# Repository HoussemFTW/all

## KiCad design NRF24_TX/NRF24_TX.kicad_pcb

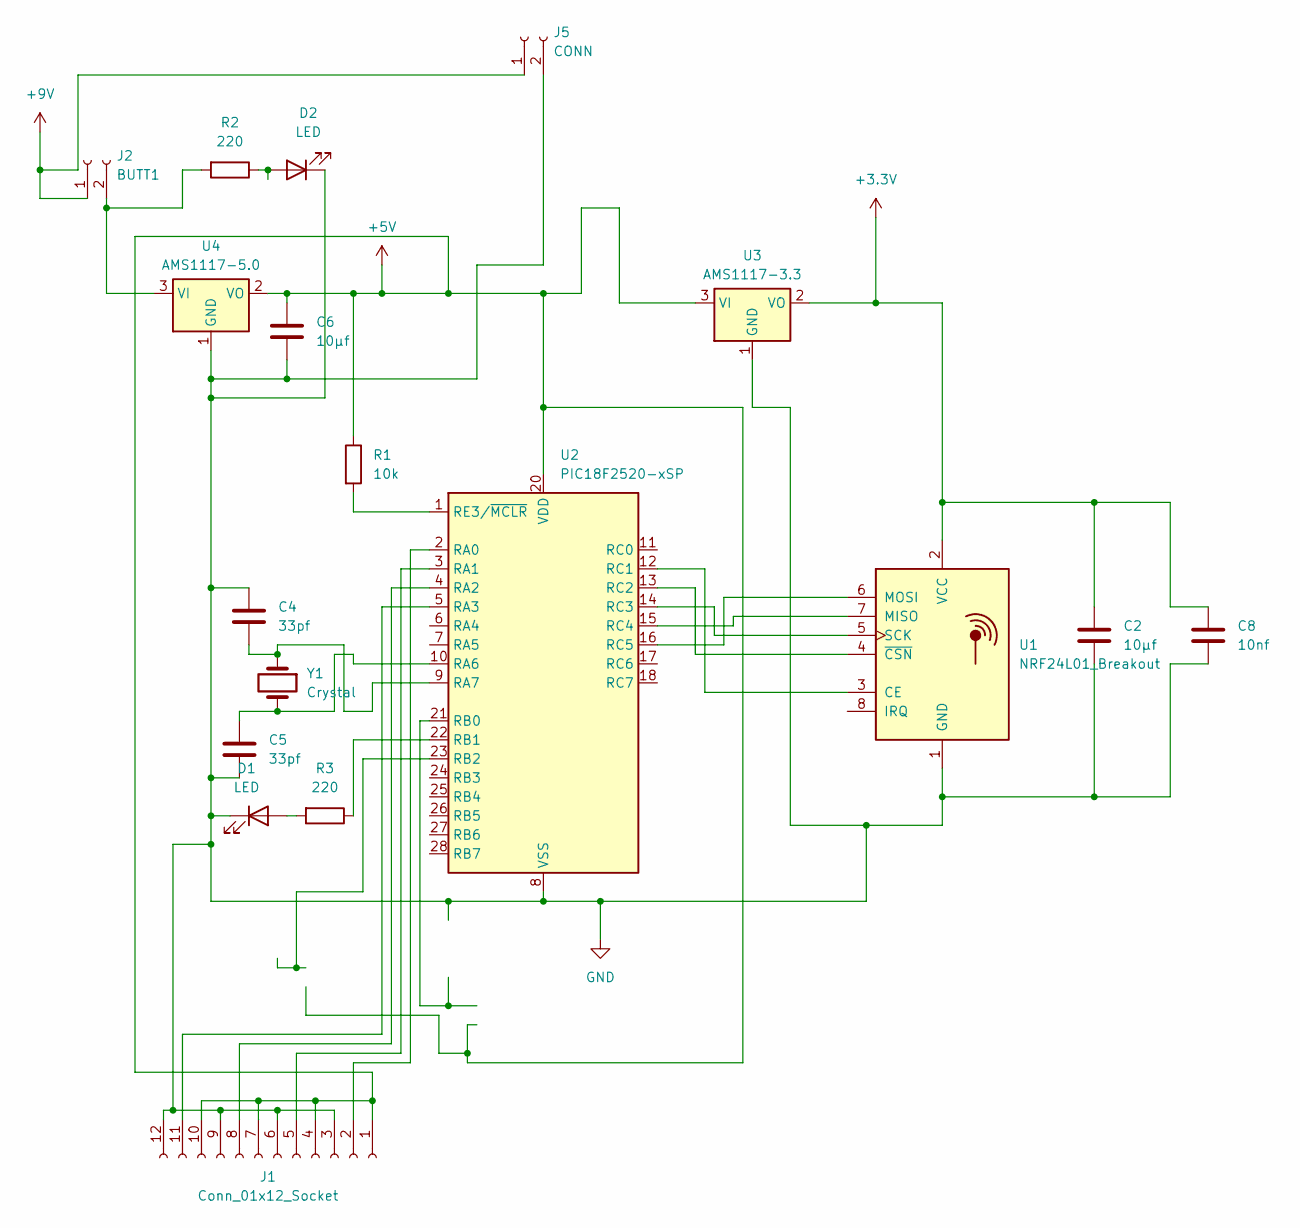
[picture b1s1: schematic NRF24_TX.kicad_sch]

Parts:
C2, C6: 10µf; CP_Radial_D4.0mm_P2.00mm
C4, C5: 33pf; C_Disc_D5.1mm_W3.2mm_P5.00mm
C8: 10nf; C_0805_2012Metric_Pad1.18x1.45mm_HandSolder
D1, D2: LED; LED_1206_3216Metric
J1: Conn_01x12_Socket; PinSocket_1x12_P2.00mm_Vertical
J2: BUTT1; PinSocket_1x02_P2.00mm_Vertical
J5: CONN; PinSocket_1x02_P2.54mm_Vertical
R1: 10k; R_Axial_DIN0207_L6.3mm_D2.5mm_P10.16mm_Horizontal
R2, R3: 220; R_1206_3216Metric_Pad1.30x1.75mm_HandSolder
U1: NRF24L01_Breakout; nRF24L01_Breakout
U2: PIC18F2520-xSP; DIP787W46P254L3467H508Q28
U3: AMS1117-3.3; SOT-223-3_TabPin2
U4: AMS1117-5.0; SOT-223-3_TabPin2
Y1: Crystal; Crystal_HC49-U_Vertical

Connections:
+3.3V: C2.1, C8.1, U1.2 (VCC), U3.2 (VO)
+5V: C6.1, J1.1, J1.4, J1.7, J1.10, R1.1, U2.20 (VDD), U3.3 (VI), U4.2 (VO)
+9V: J2.1, J5.1
GND: C2.2, C4.1, C5.2, C6.2, C8.2, D1.1 (K), D2.1 (K), J1.3, J1.6, J1.9, J1.12, J5.2, U1.1 (GND), U2.8 (VSS), U2.19 (VSS), U3.1 (GND), U4.1 (GND)
unnamed: D1.2 (A), R3.2
unnamed: D2.2 (A), R2.1
unnamed: J1.2, U2.2 (RA0)
unnamed: J1.5, U2.3 (RA1)
unnamed: J1.8, U2.4 (RA2)
unnamed: J1.11, U2.5 (RA3)
unnamed: J2.2, R2.2, U4.3 (VI)
unnamed: U1.3 (CE), U2.12 (RC1)
unnamed: U1.7 (MISO), U2.15 (RC4)
unnamed: U1.6 (MOSI), U2.16 (RC5)
unnamed: U1.5 (SCK), U2.14 (RC3)
unnamed: U1.4 (~CSN), U2.13 (RC2)
unnamed: C5.1, U2.10 (RA6), Y1.2
unnamed: C4.2, U2.9 (RA7), Y1.1
unnamed: R3.1, U2.22 (RB1)
unnamed: R1.2, U2.1 (RE3/~MCLR)

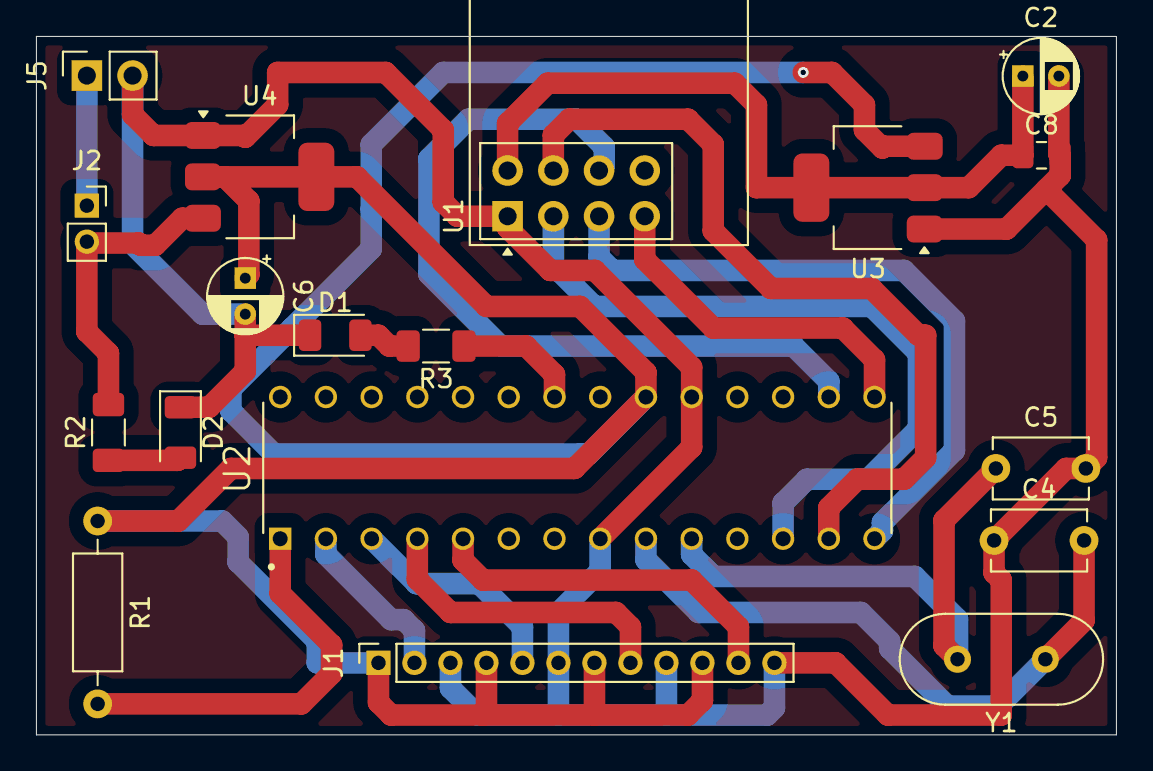
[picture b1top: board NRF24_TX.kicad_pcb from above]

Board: 2 copper layers, 60.0 x 38.8 mm, 18 parts (0 on the bottom side), 20 nets.
